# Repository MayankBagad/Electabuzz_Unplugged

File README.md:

# 🚗 Electabuzz: Line Follower Robot Hardware Platform

> **A custom hardware design, PCB layout, sensor interface, and power system package for a line-following mobile robot platform.**

Developed by **Team Electrabuzz** for *UNPLUGGED — A 24-Hour Hardware Hackathon* organized by DJSCE × IETE-ISF × DJS MicroMinds VLSI Club.

---

## 📸 Project Overview

---

## ⚡ Key Engineering Deliverables

- **Custom Form-Factor PCB**: 2-layer FR4 PCB designed in KiCad 9.0 to fit mechanical chassis boundaries, with separate ground returns for logic and motor circuits.
- **Integrated Sensor & Actuator Interface**: Onboard routing for an ESP32 microcontroller, 5-channel IR tracking array, TB6612FNG dual DC motor driver, 0.96" I²C OLED display, NEO-6M GPS, and ESP32-CAM module.
- **Dual-Domain Power Architecture**: Solar-assisted Li-ion battery charging (TP4056 + 2× 18650 cells) with LM2596 buck regulation for 5V/3.3V logic, alongside an isolated 12V motor supply rail.
- **Wide-Range Isolated Power Front-End (Simulation)**: LTSpice SPICE simulation of a $\pm 12\text{V}$ to $\pm 50\text{V}$ DC polarity-independent isolated flyback converter with logic-level polarity telemetry.
- **Design Verification**: Checked with KiCad Electrical Rules Check (ERC) and Design Rules Check (DRC).

---

## 🎯 Problem & Engineering Approach

### The Problem
Line-follower robots require clean sensor signal routing, reliable motor current delivery, and stable logic power. Connecting high-draw DC motors directly to the same unregulated battery rail as the microcontroller often causes voltage dips, electrical noise, and unwanted MCU resets.

### The Engineering Solution
**Electabuzz** addresses these requirements at the board level:
1. **Isolated Power Rails**: Logic circuitry (ESP32, sensors, OLED) is powered via an LM2596 buck regulator from 18650 Li-ion cells, while motors are driven through a dedicated 12V rail on the TB6612FNG driver.
2. **Consolidated Board Layout**: Integrates power management, compute, telemetry, and motor switching onto a single PCB shaped to match chassis mounting holes.
3. **Transient-Tolerant Power Simulation**: A supplementary flyback converter stage was modeled to evaluate polarity-independent operation and surge clamping under wide DC input ranges.

---

## 🏗 System Architecture

```
                              ┌───────────────────┐
                              │  6V Solar Panel   │
                              └─────────┬─────────┘
                                        │ (1N5819 Schottky Diode)
                                        ▼
 ┌──────────────────────┐     ┌───────────────────┐
 │ 2× 18650 Li-ion      │◄───►│  TP4056 Charger   │
 │ Battery (Parallel)   │     │ (Protection IC)   │
 └──────────────────────┘     └─────────┬─────────┘
                                        │ ~3.7V - 4.2V VBAT
                                        ▼
                              ┌───────────────────┐
                              │ LM2596 Buck Conv. │──► 5.0V Logic Rail (ESP32 VIN, CAM 5V)
                              └─────────┬─────────┘
                                        │
           ┌────────────────────────────┴────────────────────────────┐
           │                                                         │
           ▼                                                         ▼
 ┌───────────────────┐                                     ┌───────────────────┐
 │ ESP32-DEVKIT-V1   │◄────────────── UART0 ──────────────►│ ESP32-CAM (OV2640)│
 │ (Main Controller) │                                     └───────────────────┘
 └───┬───┬───┬───┬───┘
     │   │   │   │
     │   │   │   └─────────── I²C (GPIO 21/22) ───────────► 0.96" SSD1306 OLED (0x3C)
     │   │   └─────────────── UART2 (GPIO 16/17) ─────────► NEO-6M GPS Module
     │   └─────────────────── GPIO Inputs ────────────────► 5× IR Sensor Array
     │
     └─────────────────────── PWM / Direction ────────────► TB6612FNG Motor Driver
                                                                     │
                    (Dedicated 12V Motor Rail) ──────────────────────┼──► 2× 12V DC Motors
```

---

## 🔌 Hardware Interfaces & Pin Mapping

| ESP32 Pin | Connected Device | Pin / Function | Signal Type | Description |
|:---:|:---:|:---:|:---:|:---|
| **GPIO 25** | TB6612FNG | `AIN1` | Digital Out | Motor A Direction 1 |
| **GPIO 26** | TB6612FNG | `AIN2` | Digital Out | Motor A Direction 2 |
| **GPIO 27** | TB6612FNG | `PWMA` | PWM Out | Motor A Speed Control |
| **GPIO 14** | TB6612FNG | `BIN1` | Digital Out | Motor B Direction 1 |
| **GPIO 12** | TB6612FNG | `BIN2` | Digital Out | Motor B Direction 2 |
| **GPIO 13** | TB6612FNG | `PWMB` | PWM Out | Motor B Speed Control |
| **GPIO 32** | TB6612FNG | `STBY` | Digital Out | Driver Enable / Standby ($10\text{ k}\Omega$ pull-up) |
| **GPIO 21** | SSD1306 OLED | `SDA` | I²C Data | Display I²C Data line ($4.7\text{ k}\Omega$ pull-up) |
| **GPIO 22** | SSD1306 OLED | `SCL` | I²C Clock | Display I²C Clock line ($4.7\text{ k}\Omega$ pull-up) |
| **GPIO 16** | NEO-6M GPS | `TX` | UART RX2 | Serial GPS telemetry input |
| **GPIO 17** | NEO-6M GPS | `RX` | UART TX2 | Serial configuration output |
| **GPIO 34** | IR Sensor 1 | `OUT` | Digital In | Leftmost line sensor |
| **GPIO 35** | IR Sensor 2 | `OUT` | Digital In | Mid-left line sensor |
| **GPIO 36** | IR Sensor 3 | `OUT` | Digital In | Center line sensor |
| **GPIO 39** | IR Sensor 4 | `OUT` | Digital In | Mid-right line sensor |
| **GPIO 33** | IR Sensor 5 | `OUT` | Digital In | Rightmost line sensor |
| **GPIO 1** | ESP32-CAM | `U0RXD` | UART TX0 | Inter-module serial link |
| **GPIO 3** | ESP32-CAM | `U0TXD` | UART RX0 | Inter-module serial link |

> 📖 **Full Details**: For bus specifications and pinout notes, see [Architecture Documentation](docs/architecture.md).

---

## 🖥 PCB Design & Power Architecture

| Schematic Capture | Copper Layer Routing (Top & Bottom) |
|:---:|:---:|
|  |  |

### Power System Overview
- **Logic Domain (5V / 3.3V)**: Two 18650 Li-ion cells in parallel (~3.7V nominal) charged via a TP4056 module (with auxiliary 6V solar charging), regulated to 5.0V through an LM2596 buck converter for the ESP32 and ESP32-CAM.
- **Motor Domain (12V)**: An external 12V power source powers the TB6612FNG `VM` pin, keeping motor noise and current surges off the microcontroller supply rail.

> 📖 **Full Details**: For layer stackups, see [PCB Design](docs/pcb-design.md). For power tree analysis, see [Power System Documentation](docs/power-system.md).

---

## 🔬 LTSpice Simulation (Bonus Challenge)

As part of the hackathon's "Brownie Points" challenge, a **polarity-independent isolated flyback power supply** was designed and simulated in LTSpice.

> [!NOTE]
> **Source Disclosure**: The original hackathon repository included the simulation output waveform and schematic notes as an image (`ltspice-flyback-output.jpeg`). The standalone SPICE netlist files ([`polarity_protection_flyback.cir`](simulation/polarity_protection_flyback.cir) and [`polarity_protection_flyback.net`](simulation/polarity_protection_flyback.net)) were **reconstructed from the complete netlist text preserved in that original simulation output**, allowing the circuit to be opened and executed in standard SPICE simulators.

### Circuit Features
- **Wide Input Range ($\pm 12\text{V}$ to $\pm 50\text{V}$)**: Full-bridge Schottky rectifier guarantees positive internal voltage regardless of wire orientation.
- **Galvanic Isolation**: $100\text{kHz}$ flyback transformer ($1:1.2$ turns ratio) provides electrical isolation between primary input and output.
- **Regulated $+12.0\text{V}$ Output**: $12.7\text{V}$ Zener reference and NPN emitter follower deliver a regulated $12\text{V}$ output rail.
- **Polarity Telemetry**: Hardware comparator outputs a $0\text{V}$ (Normal) or $5\text{V}$ (Reversed) logic signal to indicate input polarity.

> 📖 **Full Details**: For stage-by-stage equations and netlists, see [Simulation Documentation](simulation/README.md).

---

## 📁 Repository Structure

```
Electabuzz_Unplugged/
├── .gitignore                              # KiCad, LTSpice, CAD, and OS ignore rules
├── README.md                               # Project showcase and overview
│
├── docs/                                  # Technical documentation
│   ├── architecture.md                    # System block diagrams & pin assignments
│   ├── hardware.md                        # Component specifications & mounting
│   ├── pcb-design.md                      # KiCad layout, stackup & ERC/DRC details
│   ├── power-system.md                    # Power tree & domain separation analysis
│   ├── simulation.md                      # Simulation challenge summary
│   ├── bom/                               # Manufacturing Bill of Materials
│   │   ├── README.md                      # Verified component list
│   │   ├── Bill_of_Materials.docx         # Original DOCX BOM
│   │   └── BOM.pdf                        # Original PDF BOM
│   └── assets/images/                     # Design screenshots and renders
│
├── hardware/
│   ├── pcb/                               # KiCad 9.0 PCB project files
│   │   ├── team_electrabuzz.kicad_pro     # Project master file
│   │   ├── team_electrabuzz.kicad_sch     # System schematic
│   │   └── team_electrabuzz.kicad_pcb     # PCB layout
│   └── cad/models/                        # 3D mechanical STEP models
│       ├── BK-18650-PC2--3DModel-STEP-269445.STEP
│       ├── DM-OLED096-636--3DModel-STEP-56544.STEP
│       └── MOTORJGB37-520.STEP
│
└── simulation/                            # SPICE simulation files
    ├── README.md                          # Theoretical breakdown & circuit equations
    ├── polarity_protection_flyback.cir   # Reconstructed SPICE netlist
    ├── polarity_protection_flyback.net   # LTSpice netlist format
    └── assets/images/                     # Simulation waveform plots
```

---

## 🔍 Project Scope & Future Roadmap

### Included in this Repository
- Complete KiCad 9.0 schematic, PCB layout, and design rule check reports.
- 3D STEP mechanical models for key onboard components.
- Manufacturing Bill of Materials (BOM) in Markdown, PDF, and DOCX formats.
- Reconstructed SPICE simulation netlists and theoretical documentation for the isolated power front-end.

### Future Implementation Scope (Firmware & Software)
- Microcontroller firmware for sensor reading and motor PWM generation.
- Closed-loop line tracking algorithms (e.g., PID steering control).
- Display driver routines for real-time status output on the OLED.
- ESP32-CAM firmware integration for visual data capture.

---

## 🚀 Quickstart

### Opening the PCB in KiCad
1. Install [KiCad 9.0 or higher](https://kicad.org/download/).
2. Clone this repository:
   ```bash
   git clone https://github.com/MayankBagad/Electabuzz_Unplugged.git
   ```
3. Open [`hardware/pcb/team_electrabuzz.kicad_pro`](hardware/pcb/team_electrabuzz.kicad_pro) in KiCad.

### Running the SPICE Simulation
1. Install [LTSpice](https://www.analog.com/en/resources/design-tools-and-calculators/ltspice-simulator.html) or [Ngspice](https://ngspice.sourceforge.io/).
2. Open [`simulation/polarity_protection_flyback.cir`](simulation/polarity_protection_flyback.cir).
3. Run transient analysis (`.tran 0 20m 0 1u uic`).

---

## 👥 Team & Acknowledgments

- **Team Electrabuzz** — Hardware & PCB Design, Power Architecture
- **Event**: *UNPLUGGED — 24-Hour Hardware Hackathon*
- **Organizers**: DJSCE × IETE-ISF × DJS MicroMinds VLSI Club

---

## 📄 License Notice

> [!NOTE]
> An open-source license has not yet been selected for this repository. Recommended options:
> - **Hardware Designs**: [CERN-OHL-P-2.0](https://ohwr.org/cern_ohl_p_v2.txt) (Permissive) or [CC-BY-SA-4.0](https://creativecommons.org/licenses/by-sa/4.0/)
> - **Software / Netlists**: [MIT License](https://opensource.org/licenses/MIT) or [Apache-2.0](https://www.apache.org/licenses/LICENSE-2.0)

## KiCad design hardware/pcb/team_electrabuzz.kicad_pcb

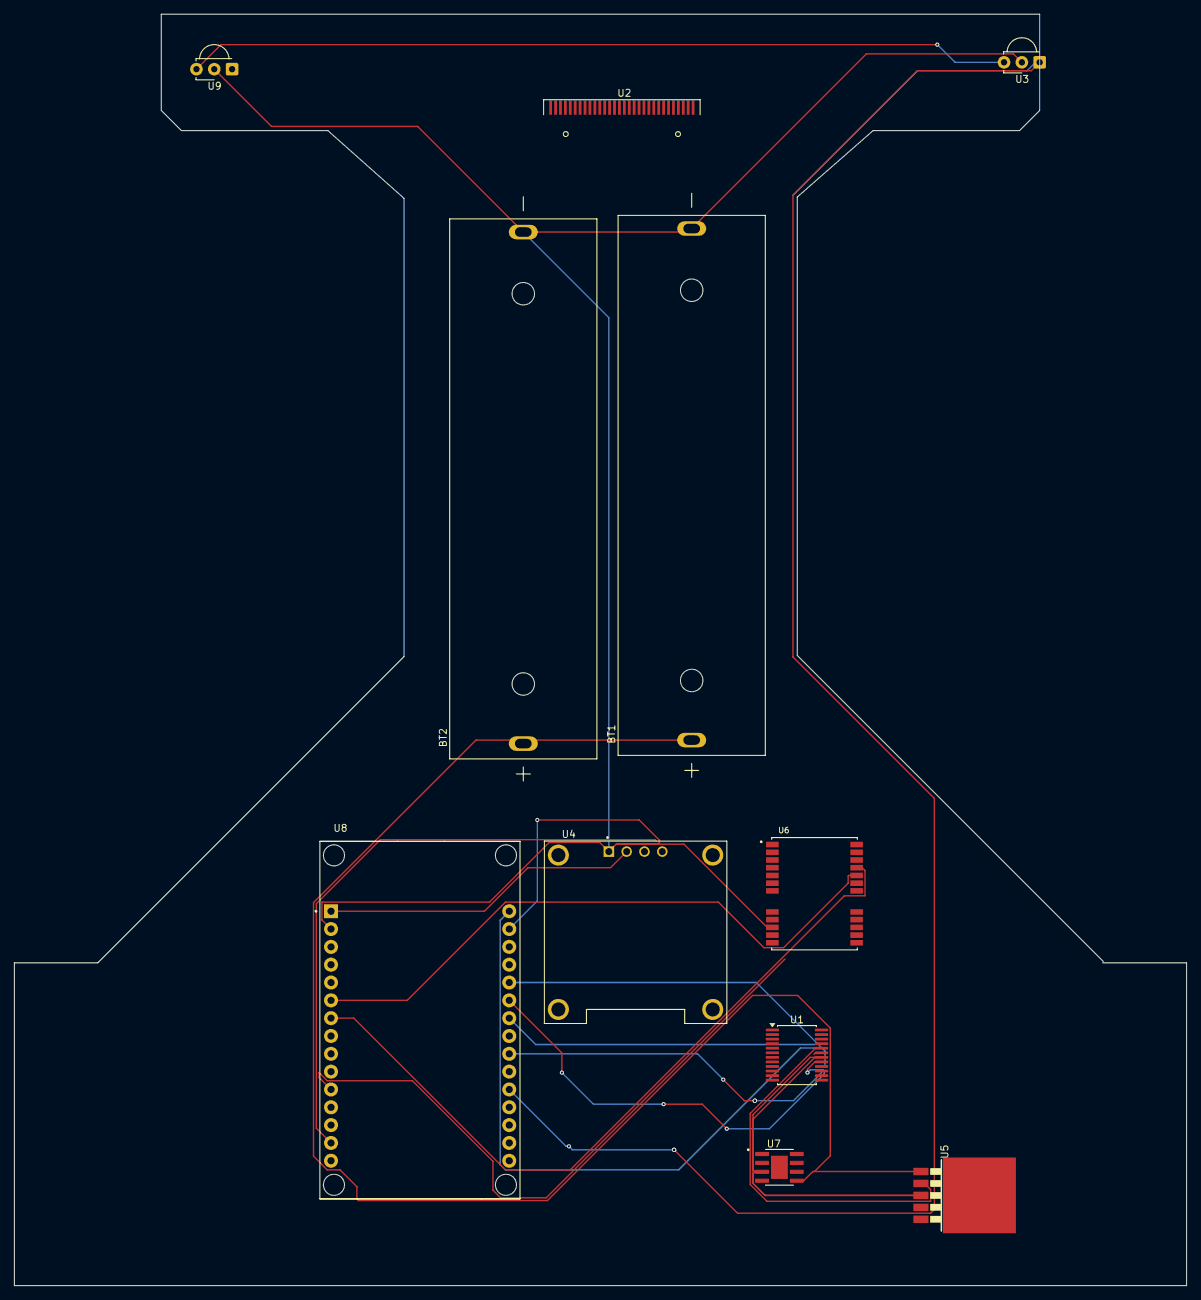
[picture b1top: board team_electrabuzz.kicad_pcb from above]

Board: 2 copper layers, 167.1 x 181.2 mm, 11 parts (0 on the bottom side), 20 nets.

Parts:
BT1, BT2: BK-18650-PC2; BAT_BK-18650-PC2
U1: TB6612FNG; SSOP-24_5.3x8.2mm_P0.65mm
U2: ESP32-CAM; OLED-128O064D
U3, U9: TSSP58038; Vishay_MINICAST-3Pin
U4: DM-OLED096-636; MODULE_DM-OLED096-636
U5: LM2596; TO263-5
U6: NEO-6M-GPS; XCVR_NEO-6M-GPS
U7: TP4056; SOP127P600X175-9N
U8: ESP32-DEVKIT-V1; MODULE_ESP32_DEVKIT_V1

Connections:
3.3v: U1.19 (STBY), U3.3 (Vs), U4.2 (VCC_IN), U6.23 (VCC), U8.1 (3V3), U9.3 (Vs)
GND: BT1.-, BT2.-, U1.18 (GND), U3.2 (GND), U4.1 (GND), U5.3 (GND), U6.10 (GND), U6.12 (GND), U6.13 (GND), U6.24 (GND), U7.3 (GND), U8.2 (GND), U8.29 (GND), U9.2 (GND)
unnamed: U1.1 (AO1), U1.2 (AO1)
unnamed: U1.5 (AO2), U1.6 (AO2)
unnamed: U1.11 (BO1), U1.12 (BO1)
unnamed: U1.7 (BO2), U1.8 (BO2)
unnamed: U1.21 (AIN1), U8.23 (D25)
unnamed: U1.22 (AIN2), U8.24 (D26)
unnamed: U1.17 (BIN1), U8.25 (D27)
unnamed: U1.16 (BIN2), U8.26 (D14)
unnamed: U1.23 (PWMA), U8.21 (D32)
unnamed: U1.15 (PWMB), U8.22 (D33)
unnamed: U1.20 (VCC), U5.2 (OUT), U8.30 (VIN)
unnamed: U3.1 (OUT), U8.20 (D35)
unnamed: U4.3 (SCL), U8.14 (D22)
unnamed: U4.4 (SDA), U8.11 (D21)
unnamed: BT1.+, BT2.+, U5.1 (VIN), U7.5 (BAT)
unnamed: U6.21 (RXD1), U8.7 (TX2)
unnamed: U6.20 (TXD1), U8.6 (RX2)
unnamed: U8.19 (D34), U9.1 (OUT)

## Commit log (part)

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2026-04-11 Rename BK-18650-PC2--3DModel-STEP-269445.STEP to MODELS/BK.STEP
2026-04-11 Rename DM-OLED096-636--3DModel-STEP-56544.STEP to MODELS/DM-OLED096-636--3DModel-STEP-56544.STEP
2026-04-11 Rename ESP32-CAM--3DModel-STEP-269445.STEP to MODELS/ESP32-CAM--3DModel-STEP-269445.STEP
2026-04-11 Rename IRsensors.STEP to MODELS/IRsensors.STEP
2026-04-11 Rename MOTORJGB37-520.STEP to MODELS/MOTORJGB37-520.STEP
2026-04-11 Rename YAAJ_DCDC_StepDown_LM2596_cp.step to MODELS/YAAJ_DCDC_StepDown_LM2596_cp.step
2026-04-11 Rename 'Buck Converter' to 'Buck Module' in README
2026-04-11 Rename WhatsApp Image 2026-04-11 at 2.39.57 PM.jpeg to Schematic.jpeg
2026-04-11 Rename WhatsApp Image 2026-04-11 at 2.40.34 PM.jpeg to Brownie output.jpeg
2026-04-11 Rename WhatsApp Image 2026-04-11 at 2.42.39 PM.jpeg to 3D model.jpeg
2026-04-11 Rename WhatsApp Image 2026-04-11 at 2.43.08 PM.jpeg to ERC.jpeg
2026-04-11 Rename WhatsApp Image 2026-04-11 at 2.43.33 PM.jpeg to DRC.jpeg
